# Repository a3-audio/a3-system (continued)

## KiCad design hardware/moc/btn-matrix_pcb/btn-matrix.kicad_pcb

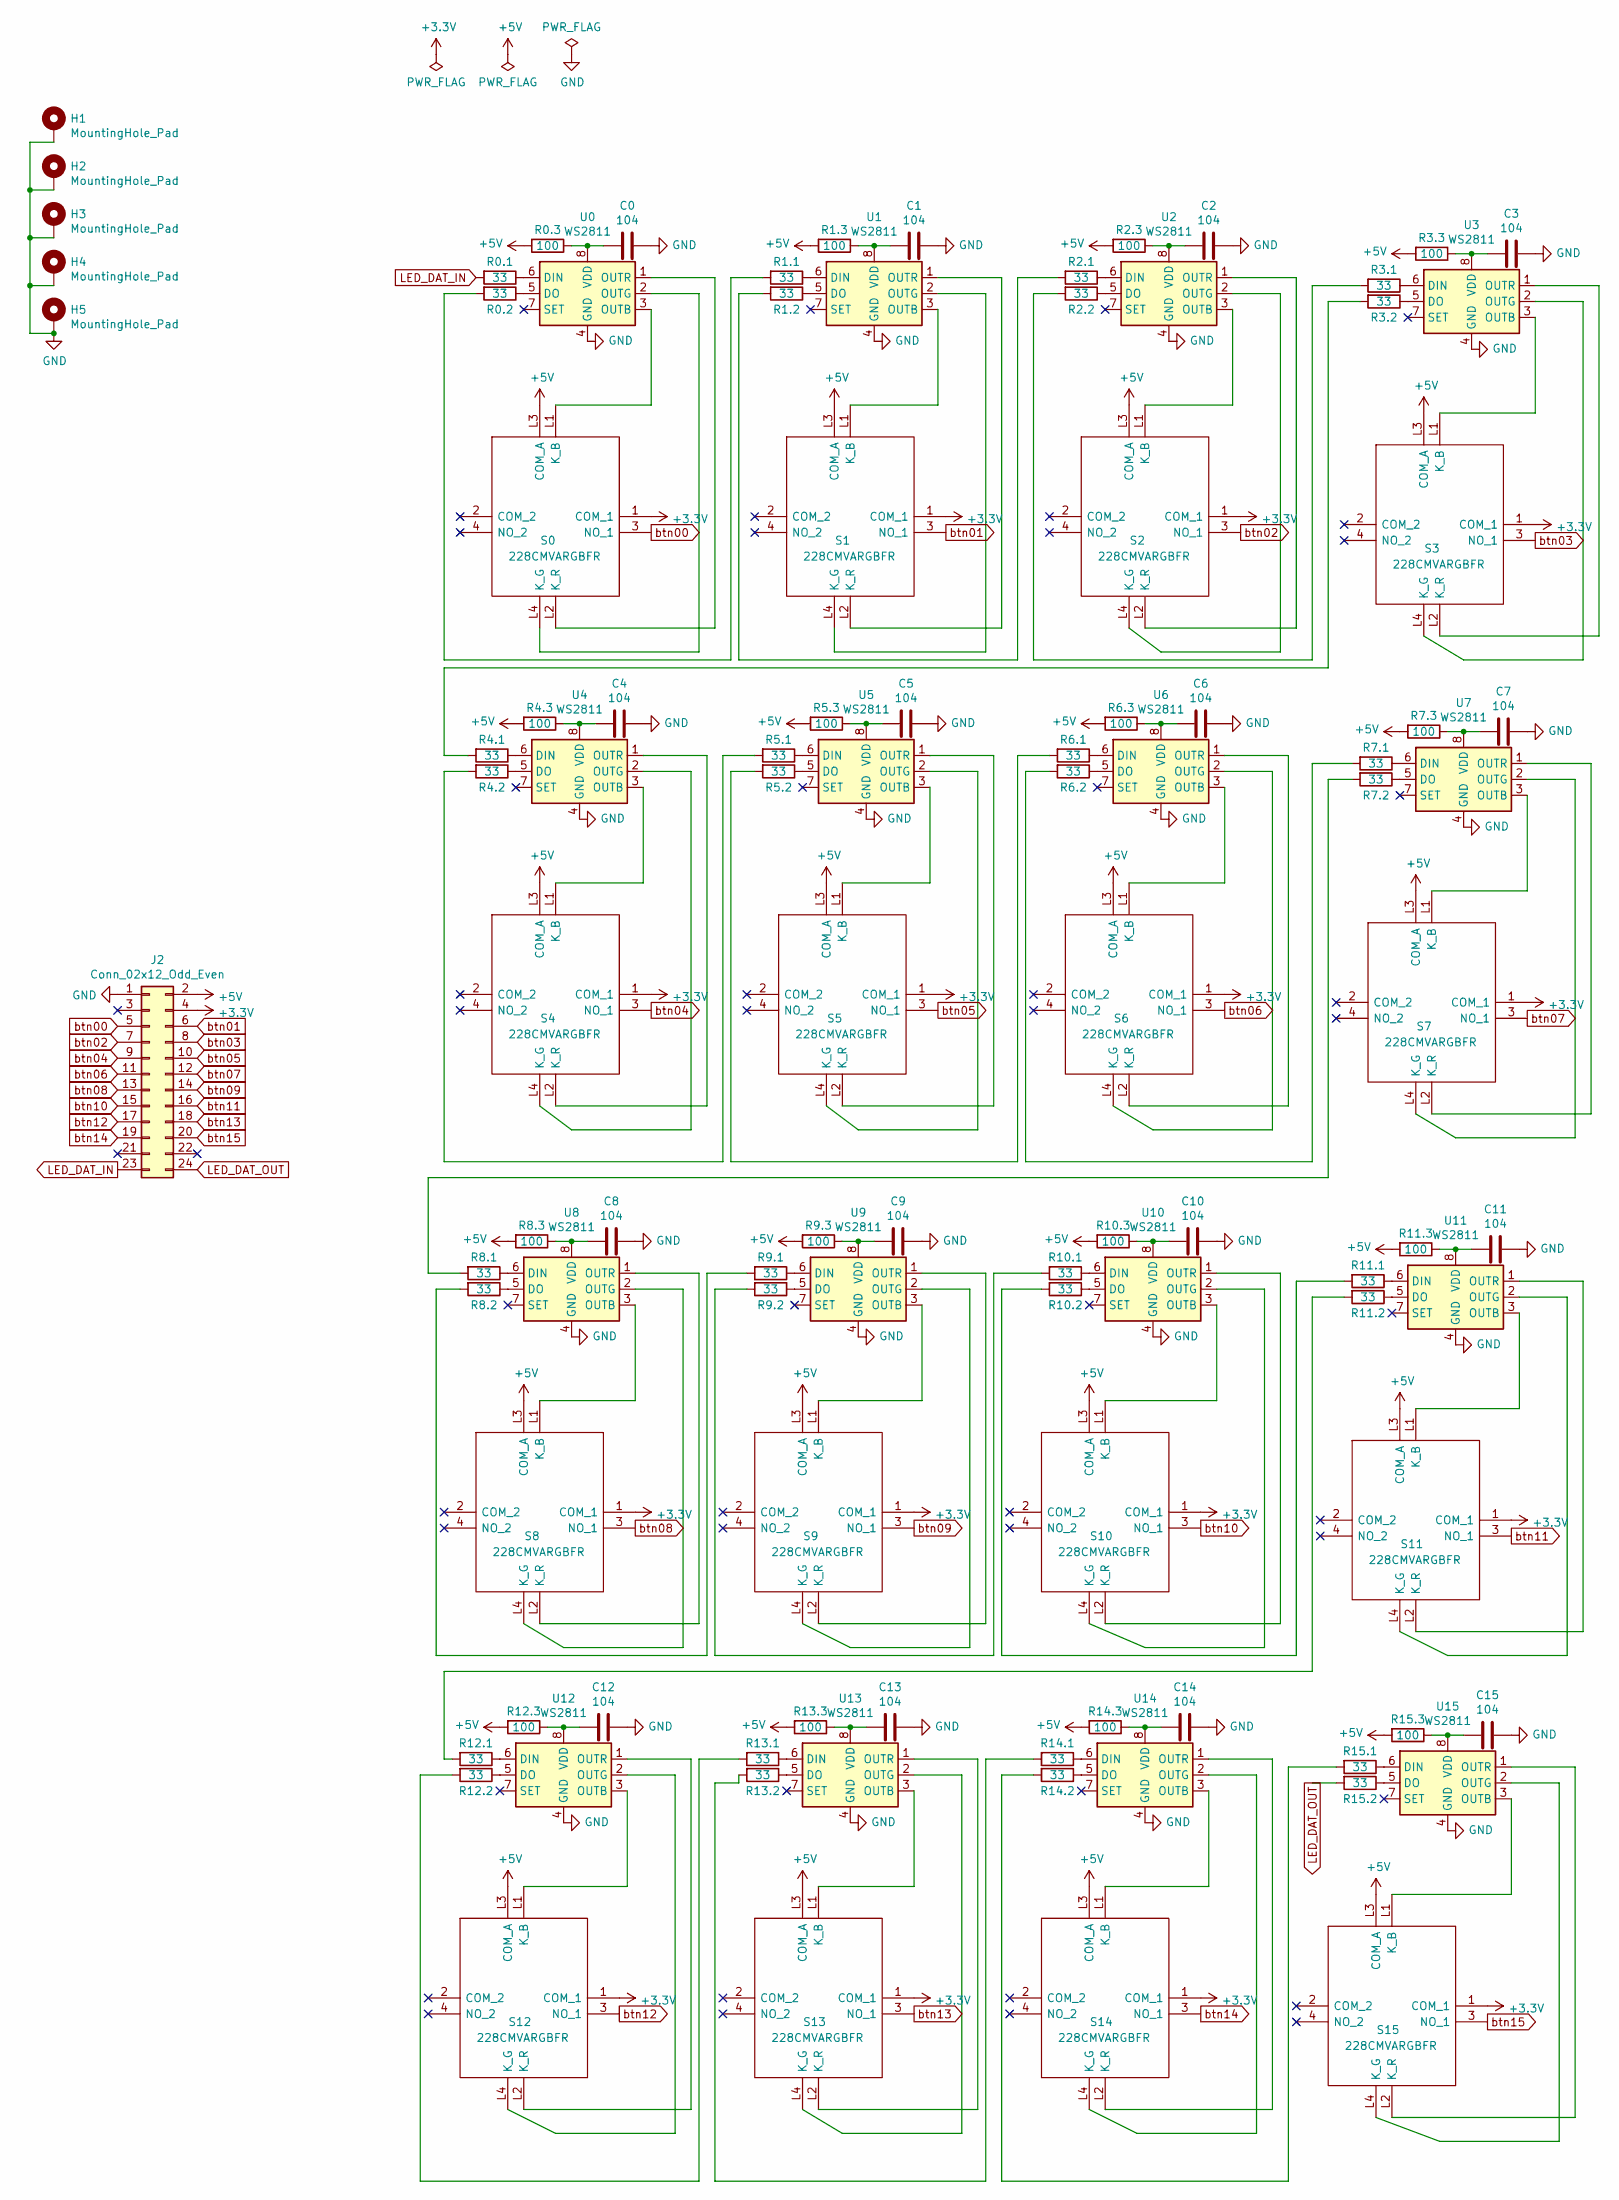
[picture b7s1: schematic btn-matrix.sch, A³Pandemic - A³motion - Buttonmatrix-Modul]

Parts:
C0, C1, C2, C3, C4, C5, C6, C7, C8, C9, C10, C11, C12, C13, C14, C15: 104; C_1206_3216Metric
H1, H2, H3, H4, H5: MountingHole_Pad; MountingHole_2.7mm_Pad_Via
J2: Conn_02x12_Odd_Even; IDC-Header_2x12_P2.54mm_Vertical
R0.1, R0.2, R1.1, R1.2, R2.1, R2.2, R3.1, R3.2, R4.1, R4.2, R5.1, R5.2, R6.1, R6.2, R7.1, R7.2, R8.1, R8.2, R9.1, R9.2, R10.1, R10.2, R11.1, R11.2, R12.1, R12.2, R13.1, R13.2, R14.1, R14.2, R15.1, R15.2: 33; R_2512_6332Metric
R0.3, R1.3, R2.3, R3.3, R4.3, R5.3, R6.3, R7.3, R8.3, R9.3, R10.3, R11.3, R12.3, R13.3, R14.3, R15.3: 100; R_2512_6332Metric
S0, S1, S2, S3, S4, S5, S6, S7, S8, S9, S10, S11, S12, S13, S14, S15: 228CMVARGBFR; Mouser Part Number 774-228CMVARGBFR
U0, U1, U2, U3, U4, U5, U6, U7, U8, U9, U10, U11, U12, U13, U14, U15: WS2811; SOP-8_3.9x4.9mm_P1.27mm

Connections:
+3V3: J2.4, S0.1 (COM_1), S1.1 (COM_1), S2.1 (COM_1), S3.1 (COM_1), S4.1 (COM_1), S5.1 (COM_1), S6.1 (COM_1), S7.1 (COM_1), S8.1 (COM_1), S9.1 (COM_1), S10.1 (COM_1), S11.1 (COM_1), S12.1 (COM_1), S13.1 (COM_1), S14.1 (COM_1), S15.1 (COM_1)
+5V: J2.2, R0.3.2, R1.3.2, R2.3.2, R3.3.2, R4.3.2, R5.3.2, R6.3.2, R7.3.2, R8.3.2, R9.3.2, R10.3.2, R11.3.2, R12.3.2, R13.3.2, R14.3.2, R15.3.2, S0.L3 (COM_A), S1.L3 (COM_A), S2.L3 (COM_A), S3.L3 (COM_A), S4.L3 (COM_A), S5.L3 (COM_A), S6.L3 (COM_A), S7.L3 (COM_A), S8.L3 (COM_A), S9.L3 (COM_A), S10.L3 (COM_A), S11.L3 (COM_A), S12.L3 (COM_A), S13.L3 (COM_A), S14.L3 (COM_A), S15.L3 (COM_A)
GND: C0.2, C1.2, C2.2, C3.2, C4.2, C5.2, C6.2, C7.2, C8.2, C9.2, C10.2, C11.2, C12.2, C13.2, C14.2, C15.2, H1.1, H2.1, H3.1, H4.1, H5.1, J2.1, U0.4 (GND), U1.4 (GND), U2.4 (GND), U3.4 (GND), U4.4 (GND), U5.4 (GND), U6.4 (GND), U7.4 (GND), U8.4 (GND), U9.4 (GND), U10.4 (GND), U11.4 (GND), U12.4 (GND), U13.4 (GND), U14.4 (GND), U15.4 (GND)
LED_DAT_IN: J2.23, R0.1.2
LED_DAT_OUT: J2.24, R15.2.2
unnamed: C0.1, R0.3.1, U0.8 (VDD)
unnamed: C1.1, R1.3.1, U1.8 (VDD)
unnamed: C2.1, R2.3.1, U2.8 (VDD)
unnamed: C3.1, R3.3.1, U3.8 (VDD)
unnamed: C4.1, R4.3.1, U4.8 (VDD)
unnamed: C5.1, R5.3.1, U5.8 (VDD)
unnamed: C6.1, R6.3.1, U6.8 (VDD)
unnamed: C7.1, R7.3.1, U7.8 (VDD)
unnamed: C8.1, R8.3.1, U8.8 (VDD)
unnamed: C9.1, R9.3.1, U9.8 (VDD)
unnamed: C10.1, R10.3.1, U10.8 (VDD)
unnamed: C11.1, R11.3.1, U11.8 (VDD)
unnamed: C12.1, R12.3.1, U12.8 (VDD)
unnamed: C13.1, R13.3.1, U13.8 (VDD)
unnamed: C14.1, R14.3.1, U14.8 (VDD)
unnamed: C15.1, R15.3.1, U15.8 (VDD)
unnamed: R0.1.1, U0.6 (DIN)
unnamed: R0.2.1, U0.5 (DO)
unnamed: R0.2.2, R1.1.2
unnamed: R1.1.1, U1.6 (DIN)
unnamed: R1.2.1, U1.5 (DO)
unnamed: R1.2.2, R2.1.2
unnamed: R2.1.1, U2.6 (DIN)
unnamed: R2.2.1, U2.5 (DO)
unnamed: R2.2.2, R3.1.2
unnamed: R3.1.1, U3.6 (DIN)
unnamed: R3.2.1, U3.5 (DO)
unnamed: R3.2.2, R4.1.2
unnamed: R4.1.1, U4.6 (DIN)
unnamed: R4.2.1, U4.5 (DO)
unnamed: R4.2.2, R5.1.2
unnamed: R5.1.1, U5.6 (DIN)
unnamed: R5.2.1, U5.5 (DO)
unnamed: R5.2.2, R6.1.2
unnamed: R6.1.1, U6.6 (DIN)
unnamed: R6.2.1, U6.5 (DO)
unnamed: R6.2.2, R7.1.2
unnamed: R7.1.1, U7.6 (DIN)
unnamed: R7.2.1, U7.5 (DO)
unnamed: R7.2.2, R8.1.2
unnamed: R8.1.1, U8.6 (DIN)
unnamed: R8.2.1, U8.5 (DO)
unnamed: R8.2.2, R9.1.2
unnamed: R9.1.1, U9.6 (DIN)
unnamed: R9.2.1, U9.5 (DO)
unnamed: R10.1.1, U10.6 (DIN)
unnamed: R9.2.2, R10.1.2
unnamed: R10.2.1, U10.5 (DO)
unnamed: R10.2.2, R11.1.2
unnamed: R11.1.1, U11.6 (DIN)
unnamed: R11.2.1, U11.5 (DO)
unnamed: R11.2.2, R12.1.2
unnamed: R12.1.1, U12.6 (DIN)
unnamed: R12.2.1, U12.5 (DO)
unnamed: R12.2.2, R13.1.2
unnamed: R13.1.1, U13.6 (DIN)
unnamed: R13.2.1, U13.5 (DO)
unnamed: R13.2.2, R14.1.2
unnamed: R14.1.1, U14.6 (DIN)
unnamed: R14.2.1, U14.5 (DO)
unnamed: R14.2.2, R15.1.2
unnamed: R15.1.1, U15.6 (DIN)
unnamed: R15.2.1, U15.5 (DO)
unnamed: S0.L1 (K_B), U0.3 (OUTB)
unnamed: S0.L2 (K_R), U0.1 (OUTR)
unnamed: S0.L4 (K_G), U0.2 (OUTG)
unnamed: S1.L1 (K_B), U1.3 (OUTB)
unnamed: S1.L2 (K_R), U1.1 (OUTR)
unnamed: S1.L4 (K_G), U1.2 (OUTG)
unnamed: S2.L1 (K_B), U2.3 (OUTB)
unnamed: S2.L2 (K_R), U2.1 (OUTR)
unnamed: S2.L4 (K_G), U2.2 (OUTG)
unnamed: S3.L1 (K_B), U3.3 (OUTB)
unnamed: S3.L2 (K_R), U3.1 (OUTR)
unnamed: S3.L4 (K_G), U3.2 (OUTG)
unnamed: S4.L1 (K_B), U4.3 (OUTB)
unnamed: S4.L2 (K_R), U4.1 (OUTR)
unnamed: S4.L4 (K_G), U4.2 (OUTG)
unnamed: S5.L1 (K_B), U5.3 (OUTB)
unnamed: S5.L2 (K_R), U5.1 (OUTR)
unnamed: S5.L4 (K_G), U5.2 (OUTG)
unnamed: S6.L1 (K_B), U6.3 (OUTB)
unnamed: S6.L2 (K_R), U6.1 (OUTR)
unnamed: S6.L4 (K_G), U6.2 (OUTG)
unnamed: S7.L1 (K_B), U7.3 (OUTB)
unnamed: S7.L2 (K_R), U7.1 (OUTR)
unnamed: S7.L4 (K_G), U7.2 (OUTG)
unnamed: S8.L1 (K_B), U8.3 (OUTB)
unnamed: S8.L2 (K_R), U8.1 (OUTR)
unnamed: S8.L4 (K_G), U8.2 (OUTG)
unnamed: S9.L1 (K_B), U9.3 (OUTB)
unnamed: S9.L2 (K_R), U9.1 (OUTR)
unnamed: S9.L4 (K_G), U9.2 (OUTG)
unnamed: S10.L1 (K_B), U10.3 (OUTB)
unnamed: S10.L2 (K_R), U10.1 (OUTR)
unnamed: S10.L4 (K_G), U10.2 (OUTG)
unnamed: S11.L1 (K_B), U11.3 (OUTB)
unnamed: S11.L2 (K_R), U11.1 (OUTR)
unnamed: S11.L4 (K_G), U11.2 (OUTG)
unnamed: S12.L1 (K_B), U12.3 (OUTB)
unnamed: S12.L2 (K_R), U12.1 (OUTR)
unnamed: S12.L4 (K_G), U12.2 (OUTG)
unnamed: S13.L1 (K_B), U13.3 (OUTB)
unnamed: S13.L2 (K_R), U13.1 (OUTR)
unnamed: S13.L4 (K_G), U13.2 (OUTG)
unnamed: S14.L1 (K_B), U14.3 (OUTB)
unnamed: S14.L2 (K_R), U14.1 (OUTR)
unnamed: S14.L4 (K_G), U14.2 (OUTG)
unnamed: S15.L1 (K_B), U15.3 (OUTB)
unnamed: S15.L2 (K_R), U15.1 (OUTR)
unnamed: S15.L4 (K_G), U15.2 (OUTG)
btn00: J2.5, S0.3 (NO_1)
btn01: J2.6, S1.3 (NO_1)
btn02: J2.7, S2.3 (NO_1)
btn03: J2.8, S3.3 (NO_1)
btn04: J2.9, S4.3 (NO_1)
btn05: J2.10, S5.3 (NO_1)
btn06: J2.11, S6.3 (NO_1)
btn07: J2.12, S7.3 (NO_1)
btn08: J2.13, S8.3 (NO_1)
btn09: J2.14, S9.3 (NO_1)
btn10: J2.15, S10.3 (NO_1)
btn11: J2.16, S11.3 (NO_1)
btn12: J2.17, S12.3 (NO_1)
btn13: J2.18, S13.3 (NO_1)
btn14: J2.19, S14.3 (NO_1)
btn15: J2.20, S15.3 (NO_1)

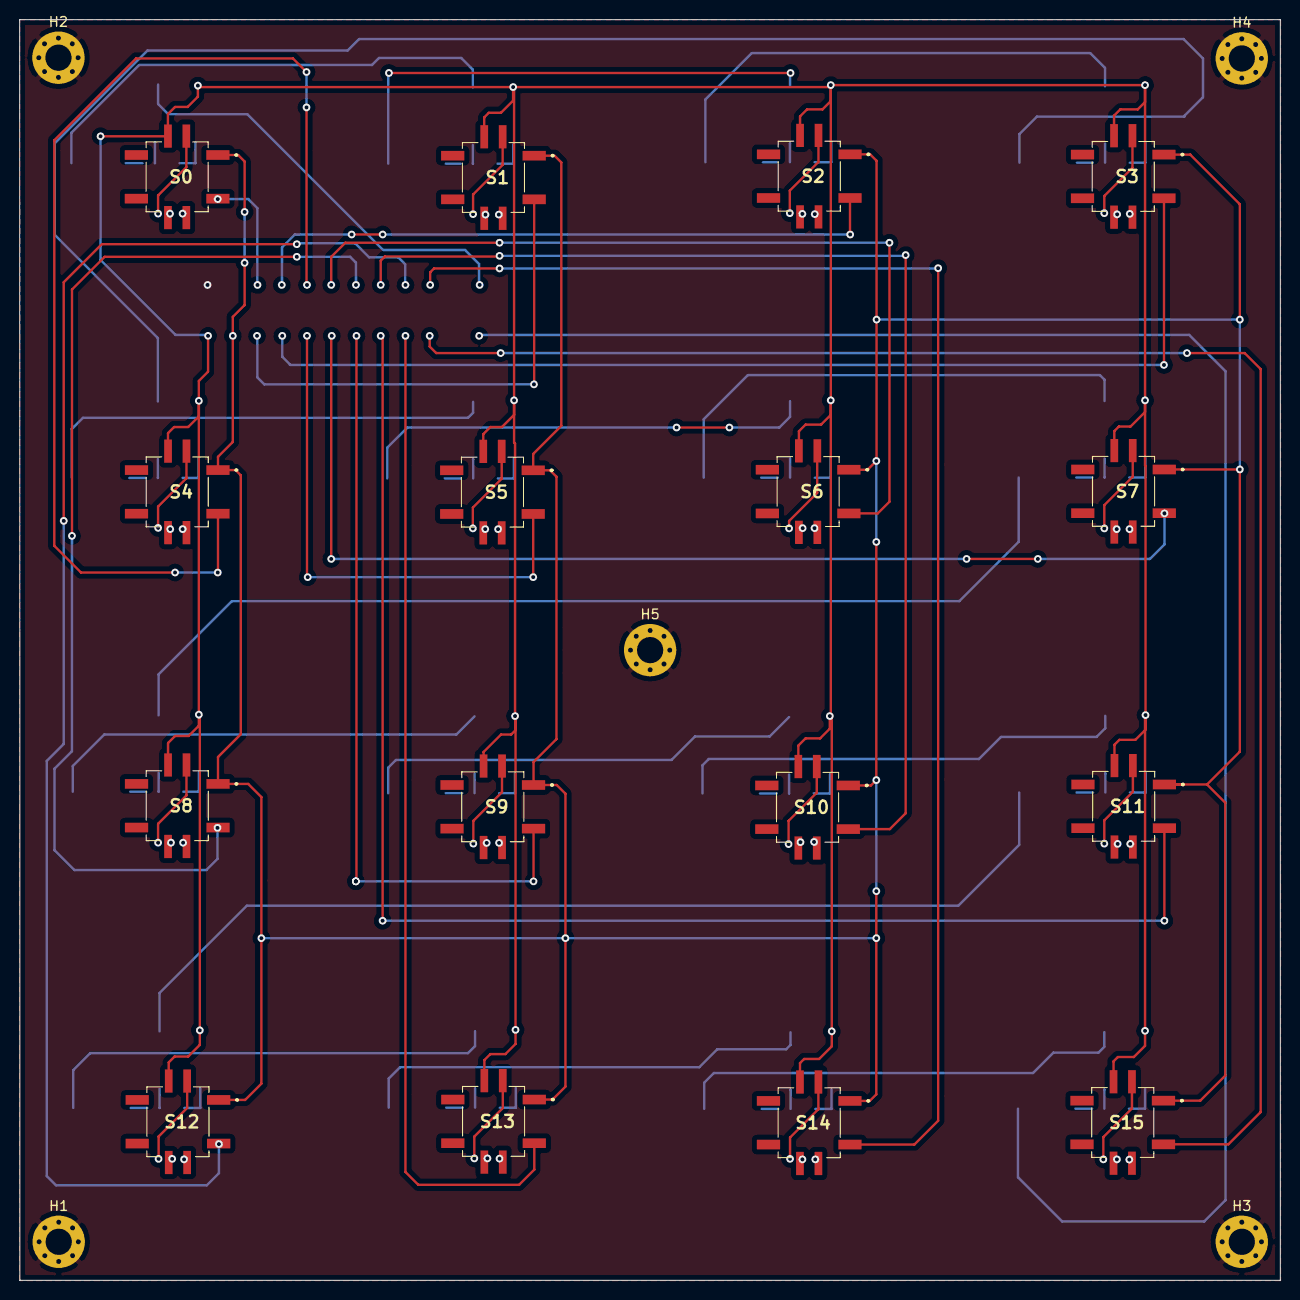
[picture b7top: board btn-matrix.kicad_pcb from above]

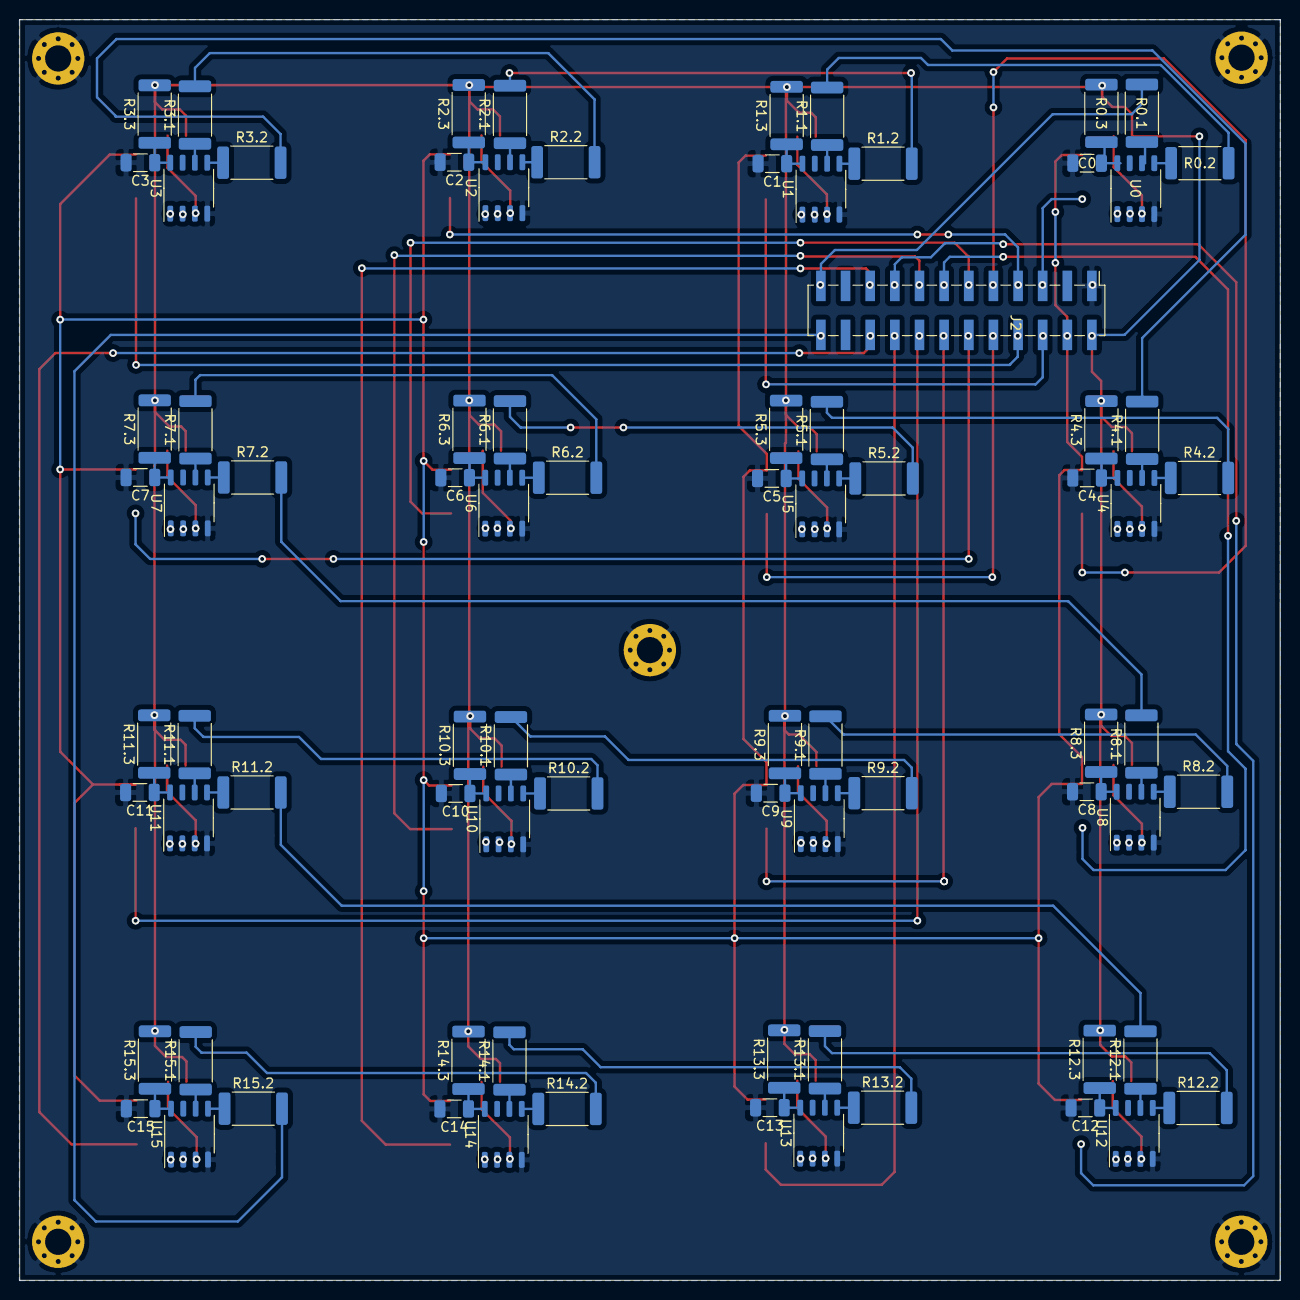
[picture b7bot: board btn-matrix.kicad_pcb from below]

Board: 2 copper layers, 130.0 x 130.0 mm, 102 parts (81 on the bottom side), 132 nets.

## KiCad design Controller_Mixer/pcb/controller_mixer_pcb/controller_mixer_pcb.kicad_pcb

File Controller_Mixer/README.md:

This file is a part of A³Pandemic. License is GPLv3: https://github.com/ambisonics-audio-association/Ambijockey/blob/main/COPYING
© Copyright 2021 Raphael Eismann, Jendrik Bradaczek 

# A³mix
## Setup
### teensy
software/teensy/src/main.cpp << flash it on your teensy 4.1 (howto: /doc/teensy_flash_fw.md)

### Raspberry
- install raspbian
- clone Ambijockey repo

#### requirements
- python3
- python-osc
- pip install numpy
- pip install process

## Start
mic.py

## Hardware
- powered with PoE -> downstep to 3V inside
- runs on raspberry pi 3b
- raspberry is connected via usb (/dev/ttyACM0) to
- teensy 4.1, it has
    - 4 multiplexer hc4051 (8ch each)
        function: audiochannel-control
        potis
        - gain 
        - eq hi
        - eq mid
        - eq low
        - volume
        mode-buttons
        - mono
        - stereo
        - ambionic
    - 1 hc4051
        function: masterchannel-control
        potis
        - master volume
        - booth volume
        - phones mix
        - headphones volume
    - 5 led-buttons for heapdphones prelisten function (pfl)
    - 1 NeoPixel-strip (ws2811 led-controller)
        - 3 leds mode-status
        - 9 leds input vu
    - 9 mode-buttons, 3 per channel
        - mono
        - stereo
        - 3d
    - 1 8x32 led-matrix for output-vu

## Open Sound Control (osc)
- receives osc messages from 
	- aaa-core/vu-meter.scd 
    - function: vu-meters
- sends osc messages to 
    - aaa-core/server.py
    - function: daw-controller, 4ch dj-mixer style
- messages /doc/osc.md

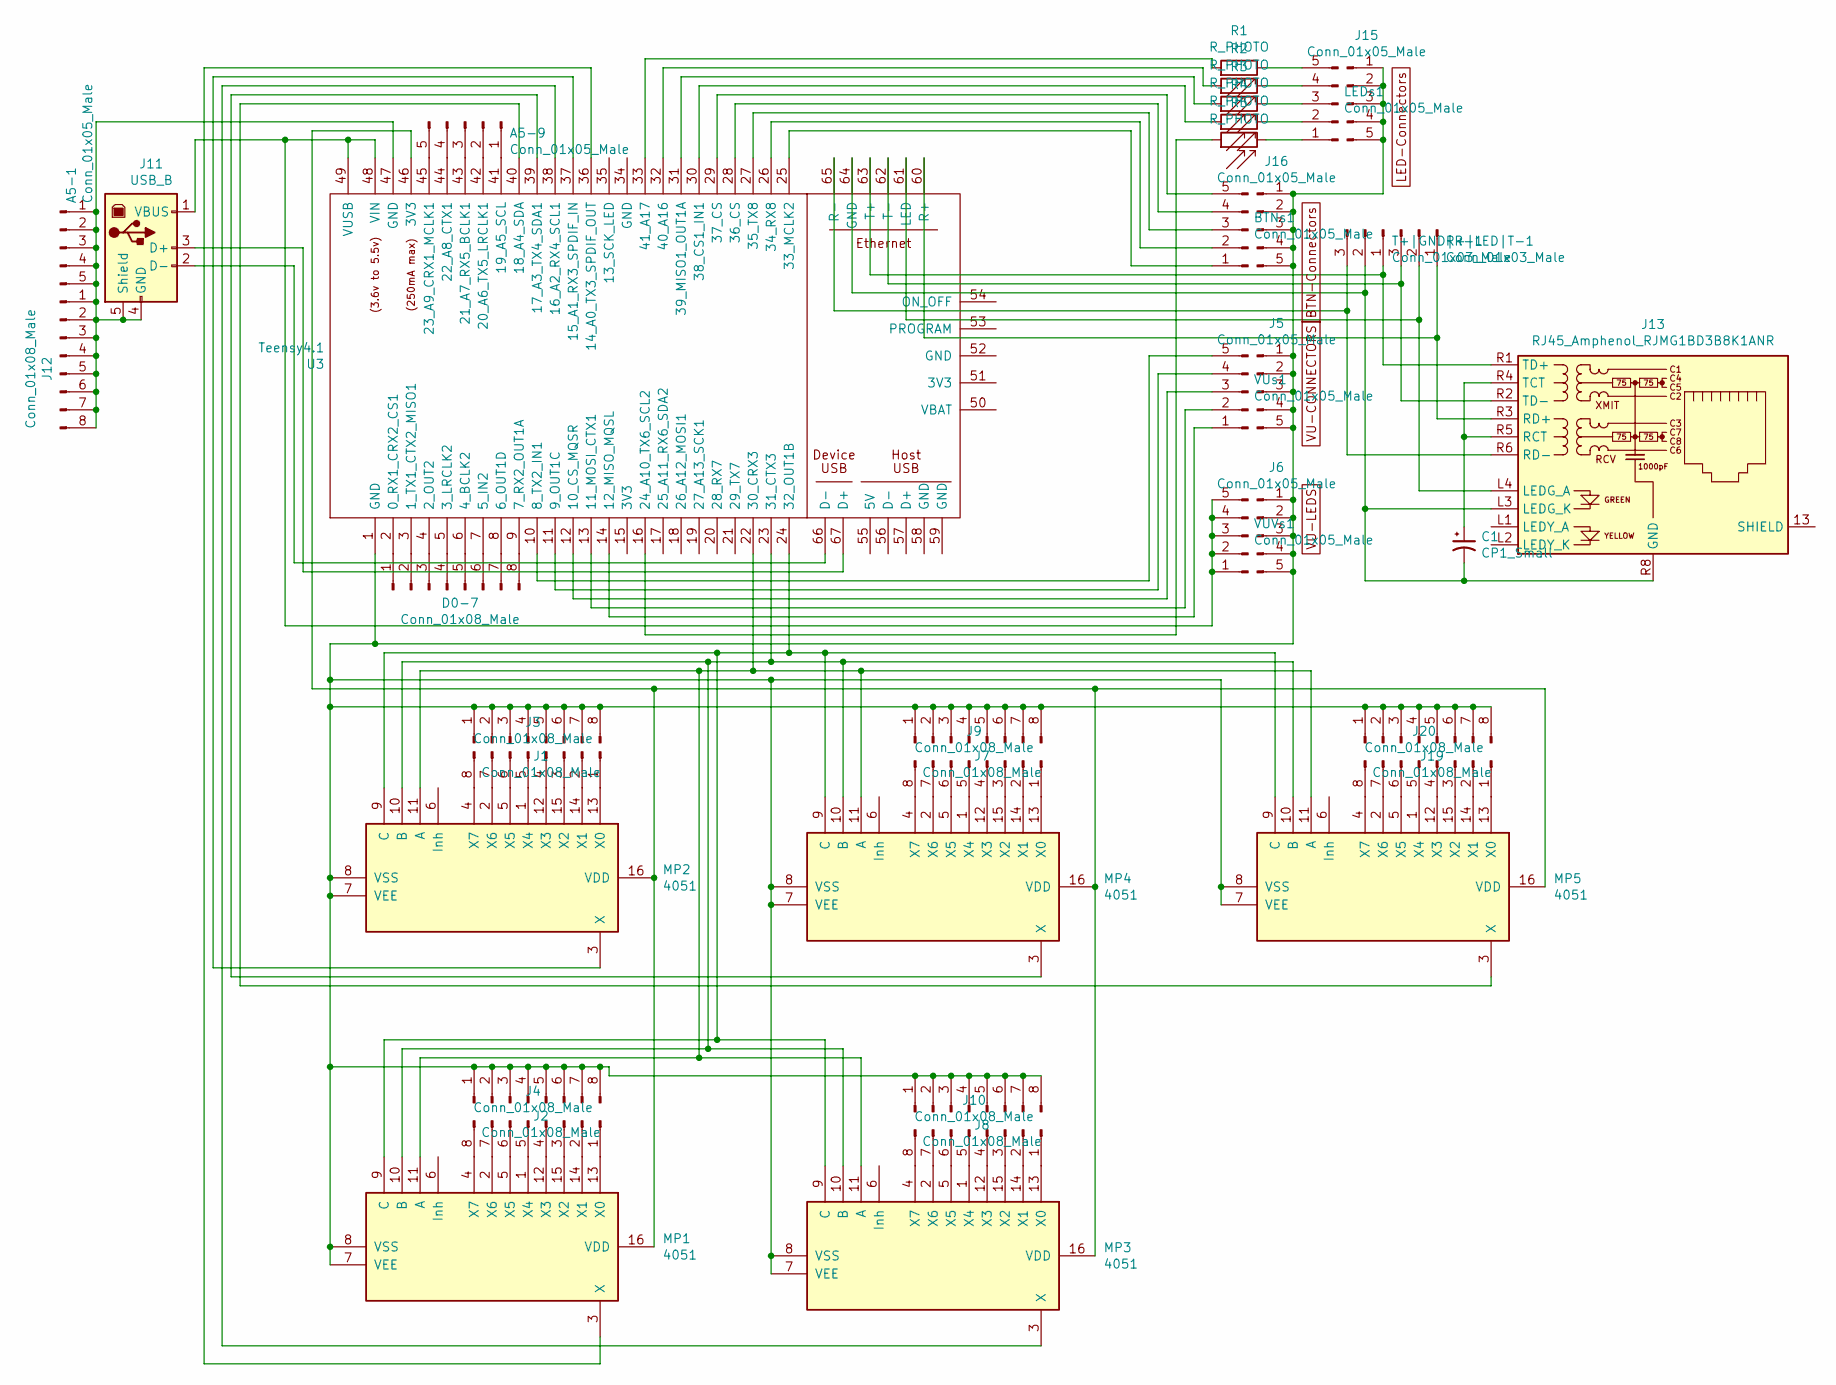
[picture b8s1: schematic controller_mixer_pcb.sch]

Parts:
A5-1, A5-9: Conn_01x05_Male; PinHeader_1x05_P2.54mm_Vertical
BTNs1: Conn_01x05_Male; PinHeader_1x05_P2.54mm_Vertical
C1: CP1_Small; CP_Axial_L10.0mm_D4.5mm_P15.00mm_Horizontal
D0-7: Conn_01x08_Male; PinHeader_1x08_P2.54mm_Vertical
J1, J2, J3, J4, J7, J8, J9, J10, J12, J19, J20: Conn_01x08_Male; PinHeader_1x08_P2.54mm_Vertical
J5, J6, J15, J16: Conn_01x05_Male; PinHeader_1x05_P2.54mm_Vertical
J11: USB_B; USB_B_Lumberg_2411_02_Horizontal
J13: RJ45_Amphenol_RJMG1BD3B8K1ANR
LEDs1: Conn_01x05_Male; PinHeader_1x05_P2.54mm_Vertical
MP1, MP2, MP3, MP4, MP5: 4051; DIP-16_W7.62mm
R1, R2, R3, R4, R5: R_PHOTO; R_Axial_DIN0207_L6.3mm_D2.5mm_P5.08mm_Vertical
R+|LED|T-1: Conn_01x03_Male; PinHeader_1x03_P2.54mm_Vertical
T+|GND|R-1: Conn_01x03_Male; PinHeader_1x03_P2.54mm_Vertical
U3: Teensy4.1; Teensy41
VUVs1: Conn_01x05_Male; PinHeader_1x05_P2.54mm_Vertical
VUs1: Conn_01x05_Male; PinHeader_1x05_P2.54mm_Vertical

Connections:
unnamed: A5-1.1, A5-1.2, A5-1.3, A5-1.4, A5-1.5, J11.4 (GND), J11.5 (Shield), J12.1, J12.2, J12.3, J12.4, J12.5, J12.6, J12.7, J12.8, U3.47 (GND)
unnamed: A5-9.1, U3.41 (19_A5_SCL)
unnamed: A5-9.2, U3.42 (20_A6_TX5_LRCLK1)
unnamed: A5-9.3, U3.43 (21_A7_RX5_BCLK1)
unnamed: A5-9.4, U3.44 (22_A8_CTX1)
unnamed: A5-9.5, U3.45 (23_A9_CRX1_MCLK1)
unnamed: BTNs1.1, U3.25 (33_MCLK2)
unnamed: BTNs1.2, U3.26 (34_RX8)
unnamed: BTNs1.3, U3.27 (35_TX8)
unnamed: BTNs1.4, U3.28 (36_CS)
unnamed: BTNs1.5, U3.29 (37_CS)
unnamed: C1.1, J13.R4 (TCT), J13.R5 (RCT)
unnamed: C1.2, J13.L3 (LEDG_K), J13.R8 (GND), T+|GND|R-1.2, U3.64 (GND)
unnamed: D0-7.1, U3.2 (0_RX1_CRX2_CS1)
unnamed: D0-7.2, U3.3 (1_TX1_CTX2_MISO1)
unnamed: D0-7.3, U3.4 (2_OUT2)
unnamed: D0-7.4, U3.5 (3_LRCLK2)
unnamed: D0-7.5, U3.6 (4_BCLK2)
unnamed: D0-7.6, U3.7 (5_IN2)
unnamed: D0-7.7, U3.8 (6_OUT1D)
unnamed: D0-7.8, U3.9 (7_RX2_OUT1A)
unnamed: J1.1, J1.2, J1.3, J1.4, J1.5, J1.6, J1.7, J1.8, J2.1, J2.2, J2.3, J2.4, J2.5, J2.6, J2.7, J2.8, J5.1, J5.2, J5.3, J5.4, J5.5, J6.1, J6.2, J6.3, J6.4, J6.5, J7.1, J7.2, J7.3, J7.4, J7.5, J7.6, J7.7, J7.8, J8.1, J8.2, J8.3, J8.4, J8.5, J8.6, J8.7, J8.8, J15.1, J15.2, J15.3, J15.4, J15.5, J16.1, J16.2, J16.3, J16.4, J16.5, J19.1, J19.2, J19.3, J19.4, J19.5, J19.6, J19.7, J19.8, MP1.7 (VEE), MP1.8 (VSS), MP2.7 (VEE), MP2.8 (VSS), MP3.7 (VEE), MP3.8 (VSS), MP4.7 (VEE), MP4.8 (VSS), MP5.7 (VEE), MP5.8 (VSS), U3.1 (GND)
unnamed: J3.1, MP2.13 (X0)
unnamed: J3.2, MP2.14 (X1)
unnamed: J3.3, MP2.15 (X2)
unnamed: J3.4, MP2.12 (X3)
unnamed: J3.5, MP2.1 (X4)
unnamed: J3.6, MP2.5 (X5)
unnamed: J3.7, MP2.2 (X6)
unnamed: J3.8, MP2.4 (X7)
unnamed: J4.1, MP1.13 (X0)
unnamed: J4.2, MP1.14 (X1)
unnamed: J4.3, MP1.15 (X2)
unnamed: J4.4, MP1.12 (X3)
unnamed: J4.5, MP1.1 (X4)
unnamed: J4.6, MP1.5 (X5)
unnamed: J4.7, MP1.2 (X6)
unnamed: J4.8, MP1.4 (X7)
unnamed: J9.1, MP4.13 (X0)
unnamed: J9.2, MP4.14 (X1)
unnamed: J9.3, MP4.15 (X2)
unnamed: J9.4, MP4.12 (X3)
unnamed: J9.5, MP4.1 (X4)
unnamed: J9.6, MP4.5 (X5)
unnamed: J9.7, MP4.2 (X6)
unnamed: J9.8, MP4.4 (X7)
unnamed: J10.1, MP3.13 (X0)
unnamed: J10.2, MP3.14 (X1)
unnamed: J10.3, MP3.15 (X2)
unnamed: J10.4, MP3.12 (X3)
unnamed: J10.5, MP3.1 (X4)
unnamed: J10.6, MP3.5 (X5)
unnamed: J10.7, MP3.2 (X6)
unnamed: J10.8, MP3.4 (X7)
unnamed: J11.1 (VBUS), U3.48 (VIN), U3.49 (VUSB), VUVs1.1, VUVs1.2, VUVs1.3, VUVs1.4, VUVs1.5
unnamed: J11.2 (D-), U3.66 (D-)
unnamed: J11.3 (D+), U3.67 (D+)
unnamed: J13.L4 (LEDG_A), R+|LED|T-1.2, U3.61 (LED)
unnamed: J13.R1 (TD+), T+|GND|R-1.1, U3.63 (T+)
unnamed: J13.R2 (TD-), R+|LED|T-1.3, U3.62 (T-)
unnamed: J13.R3 (RD+), R+|LED|T-1.1, U3.60 (R+)
unnamed: J13.R6 (RD-), T+|GND|R-1.3, U3.65 (R-)
unnamed: J20.1, MP5.13 (X0)
unnamed: J20.2, MP5.14 (X1)
unnamed: J20.3, MP5.15 (X2)
unnamed: J20.4, MP5.12 (X3)
unnamed: J20.5, MP5.1 (X4)
unnamed: J20.6, MP5.5 (X5)
unnamed: J20.7, MP5.2 (X6)
unnamed: J20.8, MP5.4 (X7)
unnamed: LEDs1.1, R5.2
unnamed: LEDs1.2, R4.2
unnamed: LEDs1.3, R3.2
unnamed: LEDs1.4, R2.2
unnamed: LEDs1.5, R1.2
unnamed: MP1.3 (X), U3.36 (14_A0_TX3_SPDIF_OUT)
unnamed: MP1.9 (C), MP2.9 (C), MP3.9 (C), MP4.9 (C), MP5.9 (C), U3.24 (32_OUT1B)
unnamed: MP1.10 (B), MP2.10 (B), MP3.10 (B), MP4.10 (B), MP5.10 (B), U3.23 (31_CTX3)
unnamed: MP1.11 (A), MP2.11 (A), MP3.11 (A), MP4.11 (A), MP5.11 (A), U3.22 (30_CRX3)
unnamed: MP1.16 (VDD), MP2.16 (VDD), MP3.16 (VDD), MP4.16 (VDD), MP5.16 (VDD), U3.46 (3V3)
unnamed: MP2.3 (X), U3.37 (15_A1_RX3_SPDIF_IN)
unnamed: MP3.3 (X), U3.38 (16_A2_RX4_SCL1)
unnamed: MP4.3 (X), U3.39 (17_A3_TX4_SDA1)
unnamed: MP5.3 (X), U3.40 (18_A4_SDA)
unnamed: R1.1, U3.33 (41_A17)
unnamed: R2.1, U3.32 (40_A16)
unnamed: R3.1, U3.31 (39_MISO1_OUT1A)
unnamed: R4.1, U3.30 (38_CS1_IN1)
unnamed: R5.1, U3.16 (24_A10_TX6_SCL2)
unnamed: U3.10 (8_TX2_IN1), VUs1.5
unnamed: U3.11 (9_OUT1C), VUs1.4
unnamed: U3.12 (10_CS_MQSR), VUs1.3
unnamed: U3.13 (11_MOSI_CTX1), VUs1.2
unnamed: U3.14 (12_MISO_MQSL), VUs1.1

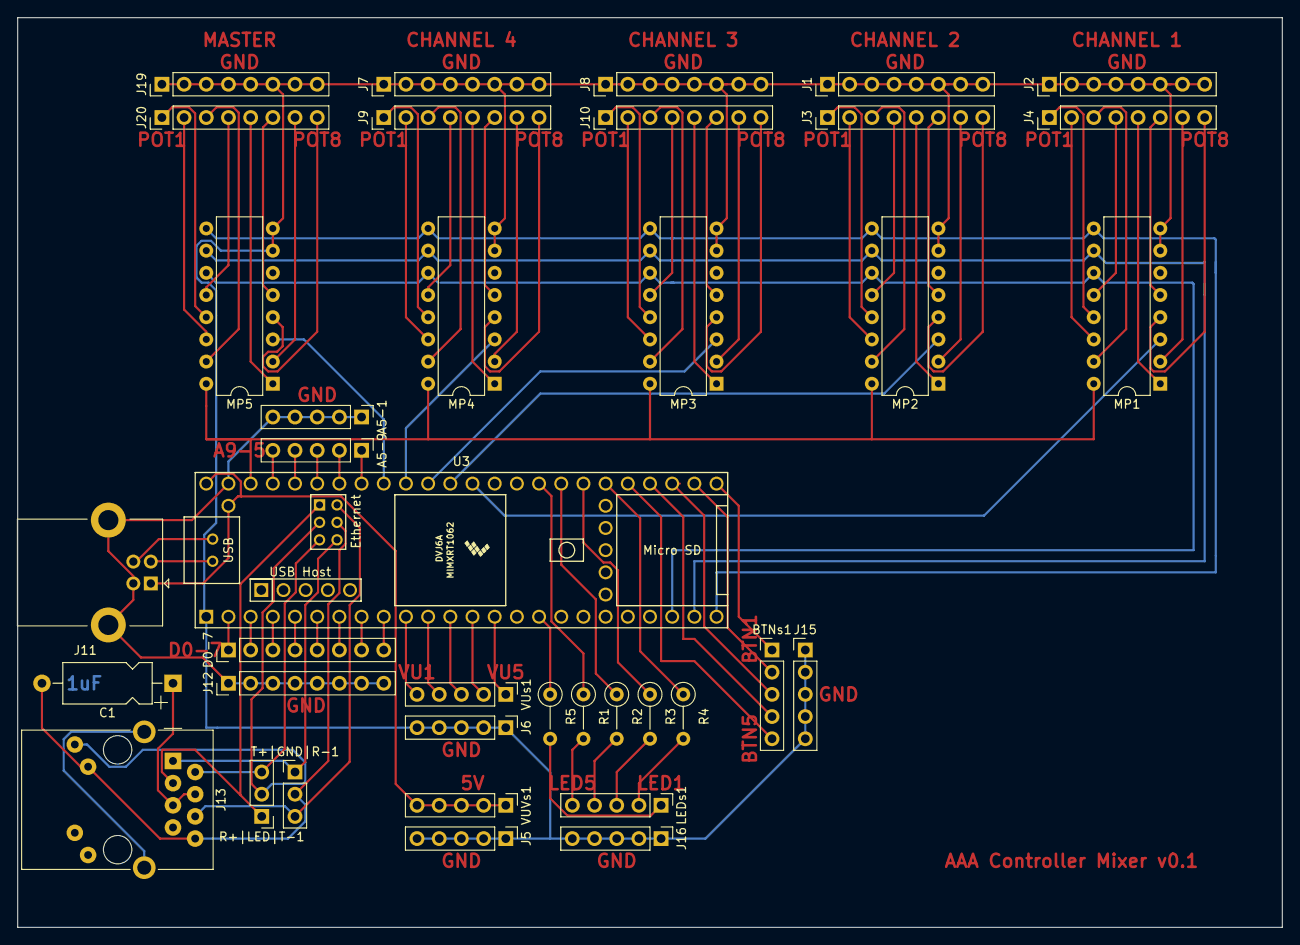
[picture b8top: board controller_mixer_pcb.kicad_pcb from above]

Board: 2 copper layers, 144.8 x 104.1 mm, 38 parts (0 on the bottom side), 94 nets.

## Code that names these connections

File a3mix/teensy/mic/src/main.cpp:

// This file is a part of A³Mix.
// License is GPLv3: https://github.com/ambisonics-audio-association/Ambijockey/blob/main/COPYING
// © Copyright 2021-2022 Raphael Eismann, Patric Schmitz

// Made for A³Mix PCB v0.2

#include <array>

#include <Arduino.h>
#include <Adafruit_NeoPixel.h>
#include <LedControl.h>

#include <Bounce.h>

const int debounce_ms = 10;
const uint8_t pin_states[2] = { HIGH, LOW };

//////////// PIN ASSIGNMENTS //////////////

const int PINS_LED_PER_CHANNEL [] = {26, 38, 39, 40};
const int PINS_BUTTON_0_PER_CHANNEL [] = {33, 34, 35, 36};
Bounce button_0_per_channel [] = {
    Bounce(PINS_BUTTON_0_PER_CHANNEL[0], debounce_ms),
    Bounce(PINS_BUTTON_0_PER_CHANNEL[1], debounce_ms),
    Bounce(PINS_BUTTON_0_PER_CHANNEL[2], debounce_ms),
    Bounce(PINS_BUTTON_0_PER_CHANNEL[3], debounce_ms)
};

const int multiplexer[6] = {5, 6, 7, 8, 9}; // Channel pots [0-3],
                                            // Master pots [4]
const int multiplexer_enc = 12; // Encoderswitches (digital)
const int selectPins[3] = {30, 31, 32}; // Multiplexer abc

// track the bounce state for 8 buttons on the multiplexer, which are
// all connected to the same teensy pin.
const int PIN_BUTTONS_1_2_MULTIPLEX_PER_CHANNEL = 27;
Bounce buttons_1_2_multiplex_per_channel [] = {
    Bounce(PIN_BUTTONS_1_2_MULTIPLEX_PER_CHANNEL, debounce_ms),
    Bounce(PIN_BUTTONS_1_2_MULTIPLEX_PER_CHANNEL, debounce_ms),
    Bounce(PIN_BUTTONS_1_2_MULTIPLEX_PER_CHANNEL, debounce_ms),
    Bounce(PIN_BUTTONS_1_2_MULTIPLEX_PER_CHANNEL, debounce_ms),
    Bounce(PIN_BUTTONS_1_2_MULTIPLEX_PER_CHANNEL, debounce_ms),
    Bounce(PIN_BUTTONS_1_2_MULTIPLEX_PER_CHANNEL, debounce_ms),
    Bounce(PIN_BUTTONS_1_2_MULTIPLEX_PER_CHANNEL, debounce_ms),
    Bounce(PIN_BUTTONS_1_2_MULTIPLEX_PER_CHANNEL, debounce_ms),
};

const int num_fx_buttons = 2;
const int PINS_BUTTON_FX [] = {28, 29};
Bounce buttons_fx [] = {
    Bounce(PINS_BUTTON_FX[0], debounce_ms),
    Bounce(PINS_BUTTON_FX[1], debounce_ms),
};

const int display_sda1 = 17;
const int display_scl1 = 16;
const int display_sda2 = 25;
const int display_scl2 = 24;

// last sent states (potis)
const int num_channels = 4;
const int num_tracks = 6; // including master and fx sections
const int num_pots = 8;
int pots_sent[num_tracks][num_pots];

const std::array<std::string, 6> track_names = {
    "0",
    "1",
    "2",
    "3",
    "master",
    "fx",
};

// vu-meter neopixel
const int npxl_pin = 13; // pcb pin
const int npxl_leds = 48;// striplength
Adafruit_NeoPixel pixels = Adafruit_NeoPixel(npxl_leds, npxl_pin, NEO_GRB + NEO_KHZ800);

int vupxlstrips[4][8] = {
    {7,6,5,4,3,2,1,0},
    {15,14,13,12,11,10,9,8},
    {23,22,21,20,19,18,17,16},
    {31,30,29,28,27,26,25,24}
};

// LED matrix
LedControl lc = LedControl(18,14,15,4); // led-matrix pins
int modePxl[4][3] = {
    {0,1,2},
    {12,13,14},
    {24,25,26},
    {36,37,38}
};

// Rotary Encoder pin mapping
// const int rEnc0_DT = 0;
// const int rEnc0_clk = 1;
// const int rEnc1_DT = 2;
// const int rEnc1_clk = 3;
// const int rEnc2_DT = 4;
// const int rEnc2_clk = 5;
// const int rEnc3_DT = 6;
// const int rEnc3_clk = 7;
// const int rEnc4_DT = 8;
// const int rEnc4_clk = 9;
// const int rEnc5_DT = 10;
// const int rEnc5_clk = 11;

// const int spare_1 = 28;
// const int spare_2 = 29;

void setup()
{

    // initialize sent values to 0
    for(int track = 0 ; track < num_tracks ; ++track) {
        for(int pot = 0 ; pot < num_pots ; ++pot) {
            pots_sent[track][pot] = 0;
        }
    }

    Serial.begin(115200);       // starting Serial
    pixels.begin(); 		// INITIALIZE NeoPixel
    pixels.clear();
    pixels.setBrightness(10);

    // Configure per-channel digital pins
    for(int channel = 0 ; channel < num_channels ; ++channel) {
        pinMode(PINS_BUTTON_0_PER_CHANNEL[channel], INPUT);
        pinMode(PINS_LED_PER_CHANNEL[channel], OUTPUT);
    }

    for(int button = 0 ; button < num_fx_buttons ; ++button) {
        pinMode(PINS_BUTTON_FX[button], INPUT);
    }

    lc.shutdown(0,false);
    lc.shutdown(1,false);
    lc.shutdown(2,false);
    lc.shutdown(3,false);

    // Set brightness
    lc.setIntensity(0,1);
    lc.setIntensity(1,1);
    lc.setIntensity(2,1);
    lc.setIntensity(3,1);
}

void loop()
{
    // first read per-track button 0 directly (no mux)
    for(int channel = 0 ; channel < num_channels ; ++channel) {
        if(button_0_per_channel[channel].update()) {
            Serial.print("T");
            Serial.print(":");
            Serial.print(channel);
            Serial.print(":");
            Serial.print("B");
            Serial.print(":0:");
            Serial.println(button_0_per_channel[channel].risingEdge() ? "1" : "0");
        }
    }

    // read pots and fx/3d buttons via hc4051 multiplexer
    for (byte pin=0 ; pin < 8 ; ++pin)
    {
        // hc4051 pinselector abc (binary)
        for (int i=0; i<3; i++) {
            digitalWrite(selectPins[i], pin & (1 << i) ? HIGH : LOW); // select hc4051
        }
        delayMicroseconds(10);

        // the four tracks [0-3] and the master track [4] are read
        // as fully analog inputs.
        for (int track=0 ; track < 5; ++track) {
            int analog = analogRead(multiplexer[track]);
            int difference = pots_sent[track][pin] - analog;

            // filter analog inputs
            // send osc when difference larger than noise on
            // last bits
            // @TODO this needs to be solved in hardware!
            if(abs(difference) > 8) {
                pots_sent[track][pin] = analog;
                float sendValue = float(analog) / 1023.f;
                Serial.print("T");
                Serial.print(":");
                Serial.print(track_names[track].c_str());
                Serial.print(":");
                Serial.print("P");
                Serial.print(":");
                Serial.print(pin);
                Serial.print(":");
                Serial.println(sendValue, 6);
            }
        }

        // read buttons 1, 2 per channel
        if(buttons_1_2_multiplex_per_channel[pin].update()) {
            Serial.print("T:");
            Serial.print(pin%4);
            Serial.print(":B:");
            Serial.print(1 + pin/4);
            Serial.print(":");
            Serial.println(buttons_1_2_multiplex_per_channel[pin].risingEdge() ? "1" : "0");
        }
    }

    // read buttons separately for FX track [5]
    for(int button = 0 ; button < num_fx_buttons ; ++button) {
        if(buttons_fx[button].update()) {
            Serial.print("T:");
            Serial.print(track_names[5].c_str());
            Serial.print(":B:");
            Serial.print(button);
            Serial.print(":");
            Serial.println(buttons_fx[button].risingEdge() ? "1" : "0");
        }
    }

    delayMicroseconds(10);

    if (Serial.available()) {
        String command = Serial.readStringUntil(':');

        if(command.equals("LED")) {
            int channel_index = Serial.readStringUntil(':').toInt();
            int led_on = Serial.readStringUntil('\n').toInt();
            digitalWrite(PINS_LED_PER_CHANNEL[channel_index], pin_states[led_on]);
        }

        if(command.equals("VU")) {
            int vu_index = Serial.readStringUntil(':').toInt();
            int peak_index = Serial.readStringUntil(':').toInt();
            int rms_index = Serial.readStringUntil('\n').toInt();

            // per-channel VU meters
            if(vu_index >= 0 && vu_index < 4) {
                int i = vu_index;
                for(int j = 0 ; j < 8 ; j++) {
                    uint32_t color;
                    if(j == peak_index)
                        color = pixels.Color(255,0,0);
                    else if(j <= rms_index)
                        color = pixels.Color(0,255,0);
                    else
                        color = pixels.Color(0,0,0);

                    pixels.setPixelColor(vupxlstrips[i][j], color);
                }
            }
            // output VU meters
            else if(vu_index >= 4 && vu_index < 12) {
                // rms-meter plus peak over all leds
                int output_vu_index = vu_index - 4;
                for(int j = 0 ; j < 32 ; j++){
                    int module_index = j / 8;
                    int x = 8 - 1 - output_vu_index;
                    int y = 8 - 1 - j % 8;

                    bool led_on = j <= rms_index || j == peak_index;
                    lc.setLed(module_index, x, y, led_on);
                }
            }
        }

        pixels.show();
    }
}

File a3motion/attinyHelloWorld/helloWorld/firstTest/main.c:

/*
 Test for moc platine
 it will blink the SCL SDA line
 pin 11 or 12
 */ 

#ifndef F_CPU			// if F_CPU was not defined in Project -> Properties
#define F_CPU 1000000UL			  // define it now as 1 MHz unsigned long
#endif

#include <avr/io.h>			  // this is always included in AVR programs
#include <util/delay.h>			  // add this to use the delay function
/*
(MALE)
1	 2	 3	 4	 5											10	 9	 8	 7	 6	 4	 3	 2
GND	SDC	SDA	UPD	VCW											SDA	SHU	ENB	BU3	AD1	AD0	ESW	BU1				(Poti Connector)
--- PB0	PB1													PB1	PB2	PB3	PB4	PB5	PA6	PA5	PA4				1	AD1
																										2	GND
																	(Attiny1626)						3	AD0
(FEMALE)					(programming interface)														4	GND	
1	 2	 3	 4	 5			 1	 2	 3						11	 12	 13	 15	 16	 17	 19					5	VCC
GND	SDC	SDA	UPD	VCW			VCW	UPD	GND						SCL	BU2	ENA	BU0	UPD	SHD	SHC		
--- PB0	PB1													PB0	PC0	PC1	PC3	PA0	PA1	PA3
															
*/

int main(void)
{
	ccp_write_io((void *) & (CLKCTRL.MCLKCTRLB), 0); //protected write to disable prescaler of CPU clock
    PORTB.DIR
	DDRB |= (1 << PB0);		  // set Port C pin PC5 for output
	
	while (1) {	                  // begin infinite loop
		PORTB ^= (1 << PB5);	  // flip state of LED on PC5
		_delay_ms(500);		  // delay 1/2 second
	}
	return(0);	// should never get here, this is to prevent a compiler warning
}
